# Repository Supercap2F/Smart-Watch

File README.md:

# Smart-Watch
A PIC Based Smart Watch

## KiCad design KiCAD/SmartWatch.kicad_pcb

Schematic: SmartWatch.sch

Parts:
C27, C28, C29, C30, C31, C33: 100n
C32: 10u; Voltage 6
C34, C35: 15p
C36, C37: 9p1
M1: MOTOR
Q1: MMBT2222A
R13, R15, R16, R17, R18, R19, R22, R23: 10K
R14: 1K
R20, R21: 4.7K
SW1, SW2, SW3, SW4: SW_PUSH
TP1, TP2, TP3, TP4, TP5, TP6, TP7, TP8: TP
U6: PIC32MX370F512H
X1: 25MHz
X2: 32.768KHz

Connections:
+3.3V: C27.1, C28.1, C29.1, C30.1, C31.1, R13.2, R20.1, R21.1, SW1.2, SW2.2, SW3.2, SW4.2, TP1.1, U6.10 (VDD), U6.19 (AVDD), U6.26 (VDD), U6.38 (VDD), U6.57 (VDD); also elsewhere on the board
/BAT/2: R22.2, R23.1, U6.17 (PGEC2/AN6/RPB6/RB6)
/LCD/Sensors/CS: U6.44 (RPD10/PMCS2/RD10); also elsewhere on the board
/LCD/Sensors/D0: U6.60 (PMD0/RE0); also elsewhere on the board
/LCD/Sensors/D1: U6.61 (PMD1/RE1); also elsewhere on the board
/LCD/Sensors/D2: U6.62 (AN20/PMD2/RE2); also elsewhere on the board
/LCD/Sensors/D3: U6.63 (RPE3/CTPLS/PMD3/RE3); also elsewhere on the board
/LCD/Sensors/D4: U6.64 (AN21/PMD4/RE4); also elsewhere on the board
/LCD/Sensors/D5: U6.1 (AN22/RPE5/PMD5/RE5); also elsewhere on the board
/LCD/Sensors/D6: U6.2 (AN23/PMD6/RE6); also elsewhere on the board
/LCD/Sensors/D7: U6.3 (AN27/PMD7/RE7); also elsewhere on the board
/LCD/Sensors/D/C: U6.30 (AN15/RPB15/OCFB/CTED6/PMA0/RB15); also elsewhere on the board
/LCD/Sensors/E: U6.52 (RPD4/PMWR/RD4); also elsewhere on the board
/LCD/Sensors/FX_RST: U6.31 (RPF4/SDA2/PMA9/RF4); also elsewhere on the board
/LCD/Sensors/INT1: U6.35 (RPF6/SCK1/INT0/RF6); also elsewhere on the board
/LCD/Sensors/INT2: U6.32 (RPF5/SCL2/PMA8/RF5); also elsewhere on the board
/LCD/Sensors/R/W: U6.53 (RPD5/PMRD/RD5); also elsewhere on the board
/LCD/Sensors/RES: U6.43 (RPD9/RD9); also elsewhere on the board
/LCD/Sensors/SCL: R20.2, TP7.1, U6.37 (SCL1/RG2); also elsewhere on the board
/LCD/Sensors/SDA: R21.2, TP8.1, U6.36 (SDA1/RG3); also elsewhere on the board
/MOTOR: R15.2, U6.18 (PGED2/AN7/RPB7/CTED3//RB7)
/RTCC: TP6.1, U6.42 (RPD8/RTCC/RD8)
/SW1: R16.2, SW1.1, U6.8 (AN19/C2INC/RPG9/PMA2/RG9)
/SW2: R17.2, SW2.1, U6.6 (AN18/C2IND/RPG8/PMA3/RG8)
/SW3: R18.2, SW3.1, U6.5 (AN17/C1INC/RPG7/PMA4/RG7)
/SW4: R19.2, SW4.1, U6.4 (AN16/C1IND/RPG6/SCK2/PMA5/RG6)
/USB/Power/Boost-En: U6.33 (RPF3/RF3); also elsewhere on the board
/USB/Power/CBUS2: U6.24 (TDO/AN11/PMA12/RB11); also elsewhere on the board
/USB/Power/CBUS4: U6.23 (TMS/CVREFOUT/AN10/RPB10/CTED11//PMA13/R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); also elsewhere on the board
/USB/Power/FTDI_RST: U6.29 (AN14/RPB14/CTED5/PMA1/RB14); also elsewhere on the board
/USB/Power/STAT1: U6.59 (RPF1/RF1); also elsewhere on the board
/USB/Power/STAT2: U6.58 (RPF0/RF0); also elsewhere on the board
/USB/Power/nPG: U6.34 (RPF2/RF2); also elsewhere on the board
GND: C27.2, C28.2, C29.2, C30.2, C31.2, C32.2, C33.2, C34.2, C35.2, C36.2, C37.2, Q1.1 (E), R16.1, R17.1, R18.1, R19.1, R23.2, TP2.1, U6.9 (Vss), U6.20 (AVss), U6.25 (Vss), U6.41 (Vss), U6.65 (Ex_Pad); also elsewhere on the board
unnamed: C34.1, U6.39 (OSC1/CLKI/RC12), X1.2
unnamed: C35.1, U6.40 (OSC2/CLKO/RC15), X1.1
unnamed: TP3.1, U6.16 (PGED1/VREF+/CVREF+/AN0/RPB0/PMA6/RB0)
unnamed: TP4.1, U6.15 (PGEC1/VREF-/CVREF-/AN1/RPB1/CTED12/RB1)
unnamed: C33.1, R13.1, R14.1
unnamed: C36.1, U6.48 (SOSCO/RPC14/T1CK/RC14), X2.2
unnamed: C37.1, U6.47 (SOSCI/RPC13/RC13), X2.1
unnamed: Q1.2 (B), R15.1
unnamed: M1.1, Q1.3 (C)
unnamed: R14.2, TP5.1, U6.7 (~MCLR)
unnamed: C32.1, U6.56 (VCAP)
VBAT: R22.1; also elsewhere on the board

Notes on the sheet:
Oscillator Configuration: FNOSC=PRIPLL // the defualt oscillator is Posc with PLL POSCMOD=HS // Posc is in HS mode FPLLIDIV=DIV_5 // divide the crystal freq. by 5 going into the PLL FPLLMUL=MUL_20 // multiply it by 20 FPLLODIV=DIV_1 // divide the output from the PLL by one Posc will be 100MHz

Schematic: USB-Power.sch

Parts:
BT1: LiPoly 1S1P
C1, C3, C8: 10u
C2, C9: 4.7u
C4: 27p
C5: 180p
C6, C10, C11, C14: 100n
C7: 1u
C12, C13: 47p
I1: 10uH
I2: 10uH
P1: CONN_6
R1: 1K
R2, R3: 0R
R4: 560K
R5: 100K
R6: 27K
R7: 2K8
R8, R9: 27R
R10: 4K7
R11: 10K
TP9, TP10, TP11: TP
U1: BQ25010
U2: MIC2290
U3: FT201X

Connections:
+3.3V: C3.1, C4.1, C7.1, C9.1, C10.1, C11.1, I1.2, I2.1, R4.2, U2.2 (VIN), U3.10 (VCC); also elsewhere on the board
+13V: C8.1, R6.1, TP9.1, U2.1 (OUT); also elsewhere on the board
/LCD/Sensors/SCL: U3.16 (SCL); also elsewhere on the board
/LCD/Sensors/SDA: U3.2 (SDA); also elsewhere on the board
/USB/Power/Boost-En: U2.3 (EN); also elsewhere on the board
/USB/Power/CBUS2: U3.5 (CBUS2); also elsewhere on the board
/USB/Power/CBUS4: U3.4 (CBUS4); also elsewhere on the board
/USB/Power/D+: C13.1, P1.3, R9.1
/USB/Power/D-: C12.1, P1.2, R8.1
/USB/Power/FTDI_RST: U3.9 (RESET); also elsewhere on the board
/USB/Power/STAT1: U1.7 (STAT1); also elsewhere on the board
/USB/Power/STAT2: U1.8 (STAT2); also elsewhere on the board
/USB/Power/USB +5V: C1.1, C6.1, P1.1, R10.2, TP10.1, U1.6 (USB)
/USB/Power/nPG: U1.14 (nPG); also elsewhere on the board
GND: BT1.2 (-), C1.2, C2.2, C3.2, C5.2, C6.2, C7.2, C8.2, C9.2, C10.2, C11.2, C12.2, C13.2, C14.2, P1.5, P1.6, R1.2, R2.2, R5.1, R7.2, R11.1, U1.3 (VSS), U1.9 (VSS), U1.15 (nCE), U1.18 (VSS), U1.20 (FPWM), U1.21 (Ex_Pad), U2.4 (AGND), U2.8 (PGND), U2.9 (Ex_Pad), U3.3 (GND), U3.13 (GND), U3.17 (GND); also elsewhere on the board
unnamed: I1.1, U1.19 (SW)
unnamed: C4.2, C5.1, R4.1, R5.2, U1.2 (FB)
unnamed: I2.2, U2.7 (SW)
unnamed: R2.1, R3.2, U1.13 (ISET2)
unnamed: R1.1, U1.12 (ISET1)
unnamed: R10.1, R11.2, U3.15 (CBUS5)
unnamed: C14.1, U3.1 (VCCIO), U3.8 (3V3OUT)
unnamed: R9.2, U3.6 (USBDP)
unnamed: R6.2, R7.1, U2.6 (FB)
unnamed: R8.2, U3.7 (USBDM)
VBAT: BT1.1 (+), C2.1, R3.1, TP11.1, U1.4 (EN), U1.16 (BAT/OUT), U1.17 (BAT/OUT); also elsewhere on the board

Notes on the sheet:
ISET1: Precharge current is determined by: I = (Vprechg * Kset)/R1 Where: Vprechg = 255mV (typ.) Kset = 322 (typ.) ISET2: Determines the battery charge rate: Asserted=500mA | De-asserted=100mA | High-Z=disable USB charging (remember the battery charge current is equal to the chage rate minus the cu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
The output voltage is determined by: Vout=Vref*((R1/R2)+1) Where: Vref=1.24V R1=R6 R2=R7

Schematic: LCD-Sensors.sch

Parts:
C15: 10u
C16, C20, C21, C22, C23, C26: 100n
C17: 4.7u; Voltage 25
C18, C24: 1u
C19, C25: 4.7u
R12: 560K
U4: EROLED015-1
U5: FXOS8700CQ

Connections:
+3.3V: C18.1, C25.1, C26.1, U4.4 (VDDIO), U4.17 (BS0), U4.18 (BS1), U4.27 (VCI); also elsewhere on the board
+13V: C15.1, C16.1, U4.2 (VCC); also elsewhere on the board
/LCD/Sensors/CS: U4.19 (CS); also elsewhere on the board
/LCD/Sensors/D0: U4.14 (D0); also elsewhere on the board
/LCD/Sensors/D1: U4.13 (D1); also elsewhere on the board
/LCD/Sensors/D2: U4.12 (D2); also elsewhere on the board
/LCD/Sensors/D3: U4.11 (D3); also elsewhere on the board
/LCD/Sensors/D4: U4.10 (D4); also elsewhere on the board
/LCD/Sensors/D5: U4.9 (D5); also elsewhere on the board
/LCD/Sensors/D6: U4.8 (D6); also elsewhere on the board
/LCD/Sensors/D7: U4.7 (D7); also elsewhere on the board
/LCD/Sensors/D/C: U4.20 (D/C); also elsewhere on the board
/LCD/Sensors/E: U4.15 (E/RD); also elsewhere on the board
/LCD/Sensors/FX_RST: U5.16 (RST); also elsewhere on the board
/LCD/Sensors/INT1: U5.11 (INT1); also elsewhere on the board
/LCD/Sensors/INT2: U5.9 (INT2); also elsewhere on the board
/LCD/Sensors/R/W: U4.16 (R/W); also elsewhere on the board
/LCD/Sensors/RES: U4.21 (RES); also elsewhere on the board
/LCD/Sensors/SCL: U5.4 (SCL/SCLK); also elsewhere on the board
/LCD/Sensors/SDA: U5.6 (SDA/MOSI); also elsewhere on the board
GND: C15.2, C16.2, C17.2, C18.2, C19.2, C20.2, C21.2, C22.2, C23.2, C24.2, C25.2, C26.2, R12.1, U4.1 (N/C_(GND)), U4.28 (VSS), U4.30 (N/C_(GND)), U5.3 (RSVR), U5.5 (GND), U5.7 (SA0/MISO), U5.10 (SA1/CS_B), U5.12 (GND), U5.13 (RSVR); also elsewhere on the board
unnamed: C19.1, C20.1, C21.1, U5.1 (VDDIO), U5.14 (VDD)
unnamed: C22.1, U5.2 (BYP)
unnamed: C23.1, U5.8 (CRST)
unnamed: R12.2, U4.22 (IREF)
unnamed: C24.1, U4.26 (VDD)
unnamed: C17.1, U4.3 (VCOMH)

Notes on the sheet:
SA0 and SA1 select the address for the chip on the I2C bus as follows: SA0=0 | SA1=0 | address=0x1E SA0=0 | SA1=1 | address=0x1D SA0=1 | SA1=0 | address=0x1C SA0=1 | SA1=1 | address=0x1F
BS0 and BS1 set the communication protocol: BS0=1 | BS1=0 | CP=3-wire SPI BS0=0 | BS1=0 | CP=4-wire SPI BS0=1 | BS1=1 | CP=68XX-parallel (8-bit) BS0=0 | BS1=1 | CP=80XX-parallel (8-bit)

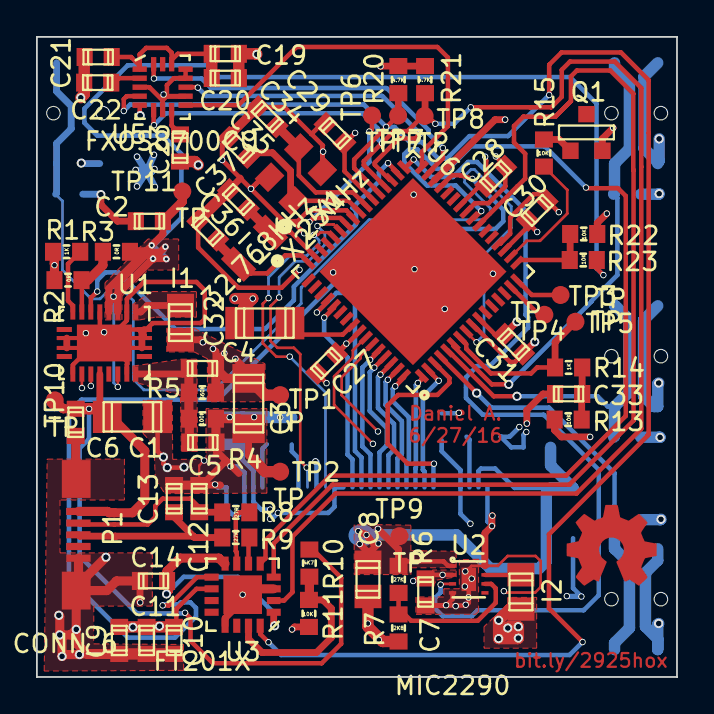
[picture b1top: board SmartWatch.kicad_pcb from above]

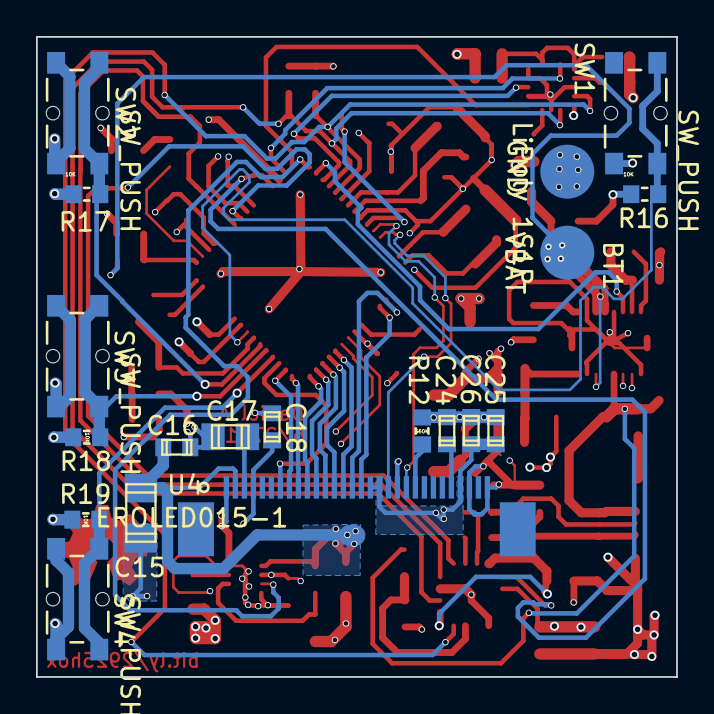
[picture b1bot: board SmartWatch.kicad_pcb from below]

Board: 4 copper layers, 35.6 x 35.6 mm, 88 parts (18 on the bottom side), 65 nets.

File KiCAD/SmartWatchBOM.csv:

LiPoly 1S1P;1;"BT1";~;~
9p1;2;"C36 C37";~;~
15p;2;"C34 C35";~;~
27p;1;"C4";~;~
47p;2;"C12 C13";~;~
180p;1;"C5";~;~
100n;16;"C6 C10 C11 C14 C16 C20 C21 C22 C23 C26 C27 C28 C29 C30 C31 C33";~;~
1u;3;"C7 C18 C24";~;~
4.7u;4;"C2 C9 C19 C25";~;~
4.7u;1;"C17";~;~;tan;25
10u;3;"C1 C3 C15";~;~
10u;1;"C8";~;~;X5R
10u;1;"C32";~;~;tan;6;<3R
10uH;1;"I1";;
10uH;1;"I2";~;~
MOTOR;1;"M1";~;~
CONN_5;1;"P1";;
NPN;1;"Q1";~;~
0R;2;"R2 R3";~;~
27R;2;"R8 R9";~;~
1K;2;"R1 R14";~;~
2K8;1;"R7";~;~
4K7;1;"R10";~;~
10K;7;"R11 R13 R15 R16 R17 R18 R19";~;~
27K;1;"R6";~;~
100K;1;"R5";~;~
560K;2;"R4 R12";~;~
SW_PUSH;4;"SW1 SW2 SW3 SW4";~;~
TP;11;"TP1 TP2 TP3 TP4 TP5 TP6 TP7 TP8 TP9 TP10 TP11";~;~
BQ25010;1;"U1";;
MIC2290;1;"U2";;
EROLED015-1;1;"U4";;
FXOS8700CQ;1;"U5";;
PIC32MX370F512H;1;"U6";;
FT201X;1;"U3";~;~
32.768KHz;1;"X2";~;~;9HT10-32.768KBZC-T
25MHz;1;"X1";~;~;ABM8-25.000MHZ-D2Y-T;50

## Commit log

2016-06-27 Finished PCB
2016-06-27 Updated PCB
2016-06-27 Updated Front Paste On PCB
2016-07-14 Created README.md
2016-07-14 Create LICENSE
2016-07-14 Added main code for Project
2016-07-14 Added Files for Bed-of-Nails
2016-07-19 Finished PCB Rev 2.0
2016-08-02 Added PDF schematic
2016-08-15 Worked out code bugs
